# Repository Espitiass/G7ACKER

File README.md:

# 🤖 G7ACKER - Robot Móvil Autónomo con Visión Artificial

Sistema de robot móvil con conducción autónoma basado en visión artificial, diseñado para navegación en entornos estructurados mediante seguimiento de carril, detección de obstáculos y dirección tipo Ackermann.

---

# 📖 Descripción del Proyecto

El proyecto consiste en el desarrollo de un robot móvil autónomo que integra procesamiento visual, sensores de proximidad y control embebido distribuido para lograr un desplazamiento inteligente sin intervención humana.

El sistema está orientado a simular escenarios reales de movilidad autónoma, como vehículos terrestres a pequeña escala que operan sobre carriles definidos.

El enfoque del proyecto combina:

- Visión artificial para percepción del entorno
- Detección de estaciones mediante sensor infrarrojo
- Control distribuido (Raspberry Pi + ESP32)
- Sistema de dirección tipo Ackermann

---

# 🎥 Demo del Sistema

## Funcionamiento del robot

> *(Agregar imágenes, GIF o enlace de video del funcionamiento)*

---

# 🔄 Flujo del Sistema

```text
[Cámara IMX219]
        ↓
[Procesamiento en Raspberry Pi (OpenCV)]
        ↓
[Decisiones de navegación]
        ↓
[ESP32]
        ↓
[Driver TB6612FNG]
        ↓
[Motores JGY-370 + Servo MG90]
```

---

# 🛠️ Hardware del Sistema

## 🧠 Unidad de procesamiento

- Raspberry Pi 5
- ESP32

---

## 📡 Sensores

- Cámara IMX219 (visión artificial)
- Sensor ultrasónico HC-SR04 (detección frontal de obstáculos)
- 1 Sensor infrarrojo TCRT5000 (detección lateral de estaciones de carga y descarga)

---

## ⚙️ Actuadores

- 2 Motores DC JGY-370
- Servo motor MG90 (engranajes metálicos)

---

## 🚗 Sistema de dirección

- Configuración tipo Ackermann

---

## ⚡ Etapa de potencia

- Driver TB6612FNG Dual Motor

---

## 🔋 Alimentación

- Batería LiPo 7.4V – 5A
- Regulador XL4016 (salida a 5V, alta corriente)
- Regulador LM2596 (salida a 3.3V)

---

# 💻 Software y Tecnologías

| Tecnología | Uso |
|---|---|
| Python | Lógica principal y visión artificial |
| OpenCV | Procesamiento de imagen |
| ESP32 (C/C++) | Control embebido |
| Serial USB | Comunicación Raspberry Pi ↔ ESP32 |

---

# 📂 Estructura del Repositorio

```text
G7ACKER/
├── .vscode/                          # Configuración de Visual Studio Code
│   └── settings.json
│
├── docs/                             # Documentación del proyecto
│   ├── acta_constitucion/
│   ├── bitacoras/
│   ├── imagenes/
│   ├── matriz_control_de_documentos/
│   ├── poster/
│   ├── presentacion_final/
│   └── README.md
│
├── hardware/                         # Diseño electrónico y PCB
│   ├── esquematico/
│   ├── pcb/
│   └── README.md
│
├── mechanical/                       # Diseño mecánico y estructural
│   ├── Diseños_de_prueba/
│   ├── Diseños_finales/
│   └── README.md
│
├── src/                              # Código fuente
│   ├── Autonomía_básica/
│   ├── Control_de_motores/
│   ├── Pruebas/
│   └── README.md
│
├── .gitignore
├── LICENSE
├── README.md
├── Scriptsactivate
└── test.jpg
```

---

# 📊 Estado del Proyecto

| Módulo | Estado |
|---|---|
| Diseño electrónico | ✅ Completado |
| PCB | ✅ Fabricada y operativa |
| Sistema mecánico | ✅ Completado |
| Visión artificial | ✅ Integrada y funcional |
| Control autónomo | 🧪 Pruebas finales |

---

# 👥 Autores

| Integrante | Área |
|---|---|
| Sofía Salomé Espitia Jiménez | Área de diseño |
| Vanesa Galeano Franco | Área de programación |
| Julián Andrés García Correa | Área eléctrica y electrónica |
| Jose Lisander Hurtado Castañeda | Área mecánica |

---

# 📄 Licencia

Este proyecto se distribuye bajo la licencia MIT License.

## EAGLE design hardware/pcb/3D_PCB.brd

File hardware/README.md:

# Diseño Electrónico

Esta carpeta contiene el desarrollo del sistema electrónico del robot G7ACKER, incluyendo el diseño del esquemático y la PCB utilizada para la integración del sistema.

---

## Estructura

```text
hardware/
│── esquematico/
│── pcb/
```

---

## Contenido

### Esquemático

Incluye la representación del sistema electrónico antes de su implementación física:

* Imagen del esquemático por medio de ilustración en el sofware DRAW.IO (formato PNG) para visualización rápida
* Archivo original del esquemático (formato `.sch`) con todas las conexiones y componentes definidos
* Imagen del esquematico original en FUSION

Este diseño permite validar la correcta interconexión de los módulos antes de avanzar al diseño de la PCB.

---

### PCB

Contiene el diseño final de la placa electrónica:

* Archivo de la PCB con ruteo completo (formato `.f3z`, Fusion 360)
* Modelo 3D de la PCB (formato `.brd`)
* Imagen del ruto de la pcb en FUSION

Este diseño corresponde a la versión enviada a fabricación, incluyendo:

* Rutas eléctricas
* Distribución de componentes
* Integración del sistema completo

---

## Propósito

* Documentar el diseño electrónico del sistema
* Facilitar la fabricación de la PCB
* Permitir la revisión y modificación del circuito
* Servir como base para futuras iteraciones

---

## Notas

* Mantener consistencia entre esquemático y PCB
* Verificar nombres de componentes y conexiones
* Evitar modificaciones directas sobre versiones finales sin control

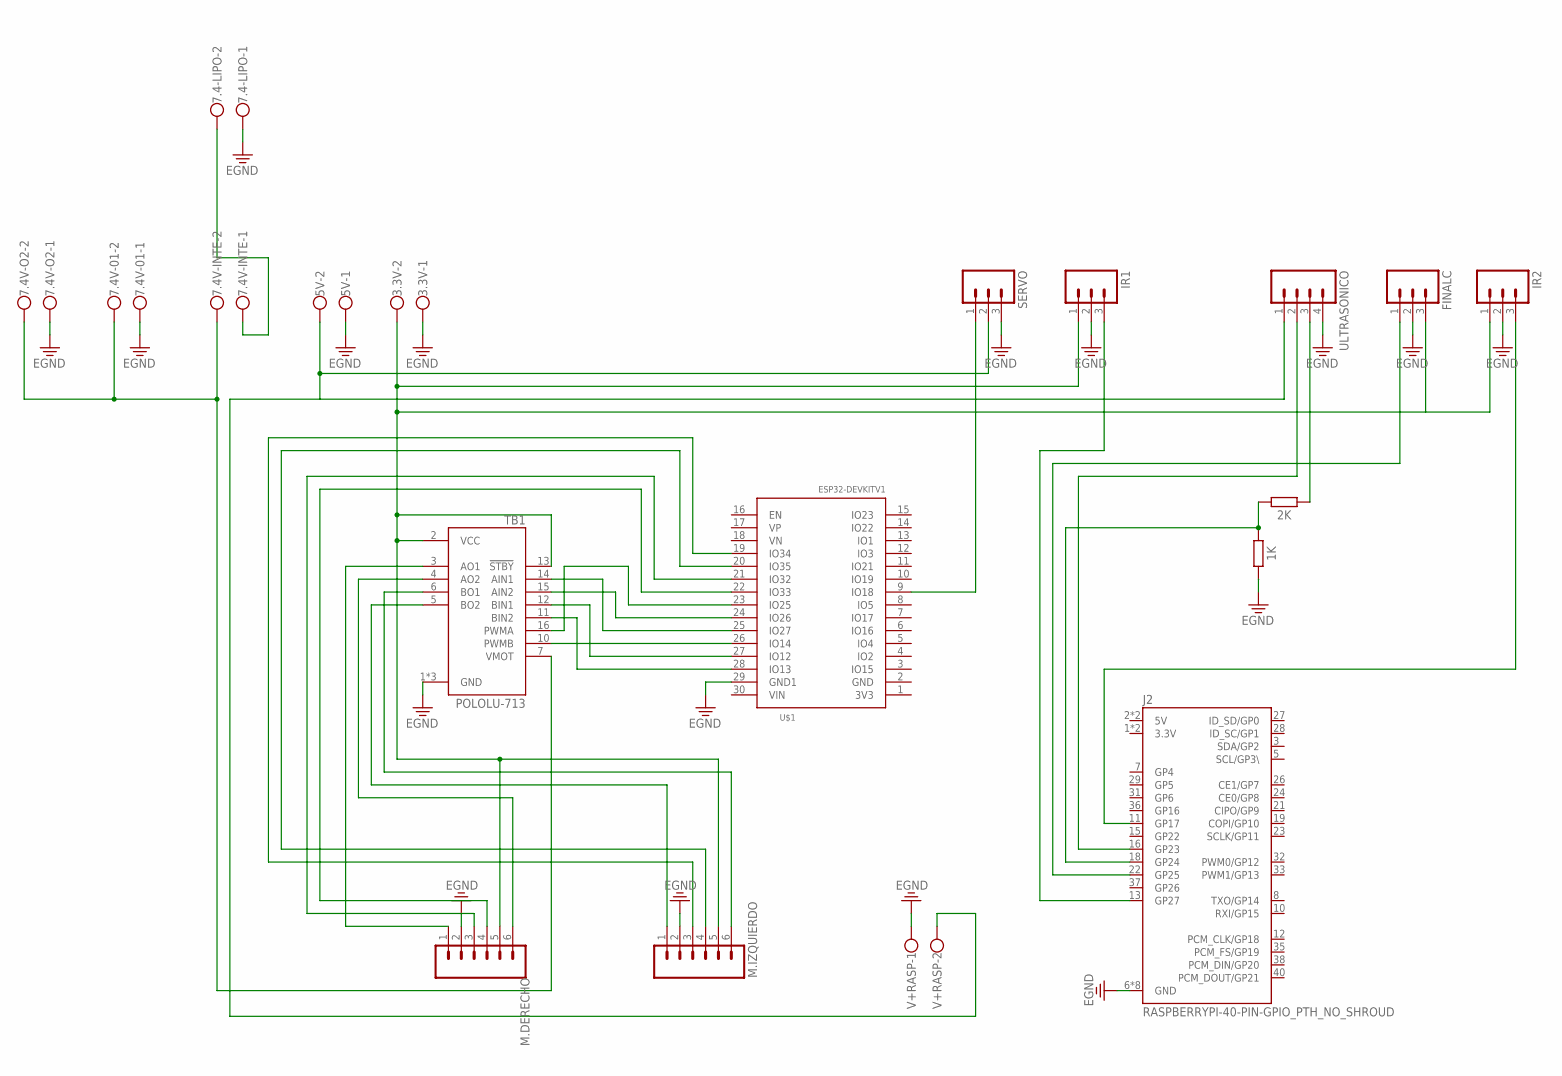
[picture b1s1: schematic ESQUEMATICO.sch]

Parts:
1K, 2K: R_AXIAL-11.7MM-PITCH; RESAD1176W63L850D250B
3.3V, 5V, 7.4-LIPO, 7.4V-01, 7.4V-INTE, 7.4V-O2: W237-102
FINALC: MA03; 03P
IR1, IR2: MA03; 03P
J2: RASPBERRYPI-40-PIN-GPIO_PTH_NO_SHROUD; 2X20
M.DERECHO, M.IZQUIERDO: MA06; 06PA
SERVO: MA03; 03P
TB1: POLOLU-713; SHIELD_POLOLU-713
U$1: ESP32DEVKITV1; ESP32-DEVKITV1
ULTRASONICO: MA04; 04PA
V+RASP: W237-102

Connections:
3.3V: 3.3V.2, FINALC.3, IR1.1, IR2.1, J2.1 (3.3V), J2.17 (3.3V), M.DERECHO.5, M.IZQUIERDO.5, TB1.2 (VCC), TB1.13 (!STBY)
5V: 5V.2, J2.2 (5V), J2.4 (5V), SERVO.2, ULTRASONICO.1, V+RASP.2
7.4V: 7.4-LIPO.2, 7.4V-INTE.1
EGND: 1K.2, 3.3V.1, 5V.1, 7.4-LIPO.1, 7.4V-01.1, 7.4V-O2.1, FINALC.2, IR1.2, IR2.2, J2.6 (GND), J2.9 (GND), J2.14 (GND), J2.20 (GND), J2.25 (GND), J2.30 (GND), J2.34 (GND), J2.39 (GND), M.DERECHO.2, M.IZQUIERDO.2, SERVO.3, TB1.1 (GND), TB1.8 (GND), TB1.9 (GND), U$1.29 (GND1), ULTRASONICO.4, V+RASP.1
M.DERECHO2: 7.4V-01.2, 7.4V-INTE.2, 7.4V-O2.2, TB1.7 (VMOT)
unnamed: TB1.16 (PWMA), U$1.23 (IO25)
unnamed: TB1.10 (PWMB), U$1.26 (IO14)
unnamed: TB1.11 (BIN2), U$1.28 (IO13)
unnamed: TB1.12 (BIN1), U$1.27 (IO12)
unnamed: TB1.15 (AIN2), U$1.24 (IO26)
unnamed: TB1.14 (AIN1), U$1.25 (IO27)
unnamed: M.DERECHO.1, TB1.3 (AO1)
unnamed: M.DERECHO.6, TB1.4 (AO2)
unnamed: M.IZQUIERDO.6, TB1.6 (BO1)
unnamed: M.IZQUIERDO.1, TB1.5 (BO2)
unnamed: M.DERECHO.3, U$1.21 (IO32)
unnamed: M.DERECHO.4, U$1.22 (IO33)
unnamed: M.IZQUIERDO.3, U$1.19 (IO34)
unnamed: M.IZQUIERDO.4, U$1.20 (IO35)
unnamed: SERVO.1, U$1.9 (IO18)
unnamed: IR2.3, J2.11 (GP17)
unnamed: IR1.3, J2.13 (GP27)
unnamed: J2.16 (GP23), ULTRASONICO.2
unnamed: FINALC.1, J2.22 (GP25)
unnamed: 1K.1, 2K.2, J2.18 (GP24)
unnamed: 2K.1, ULTRASONICO.3

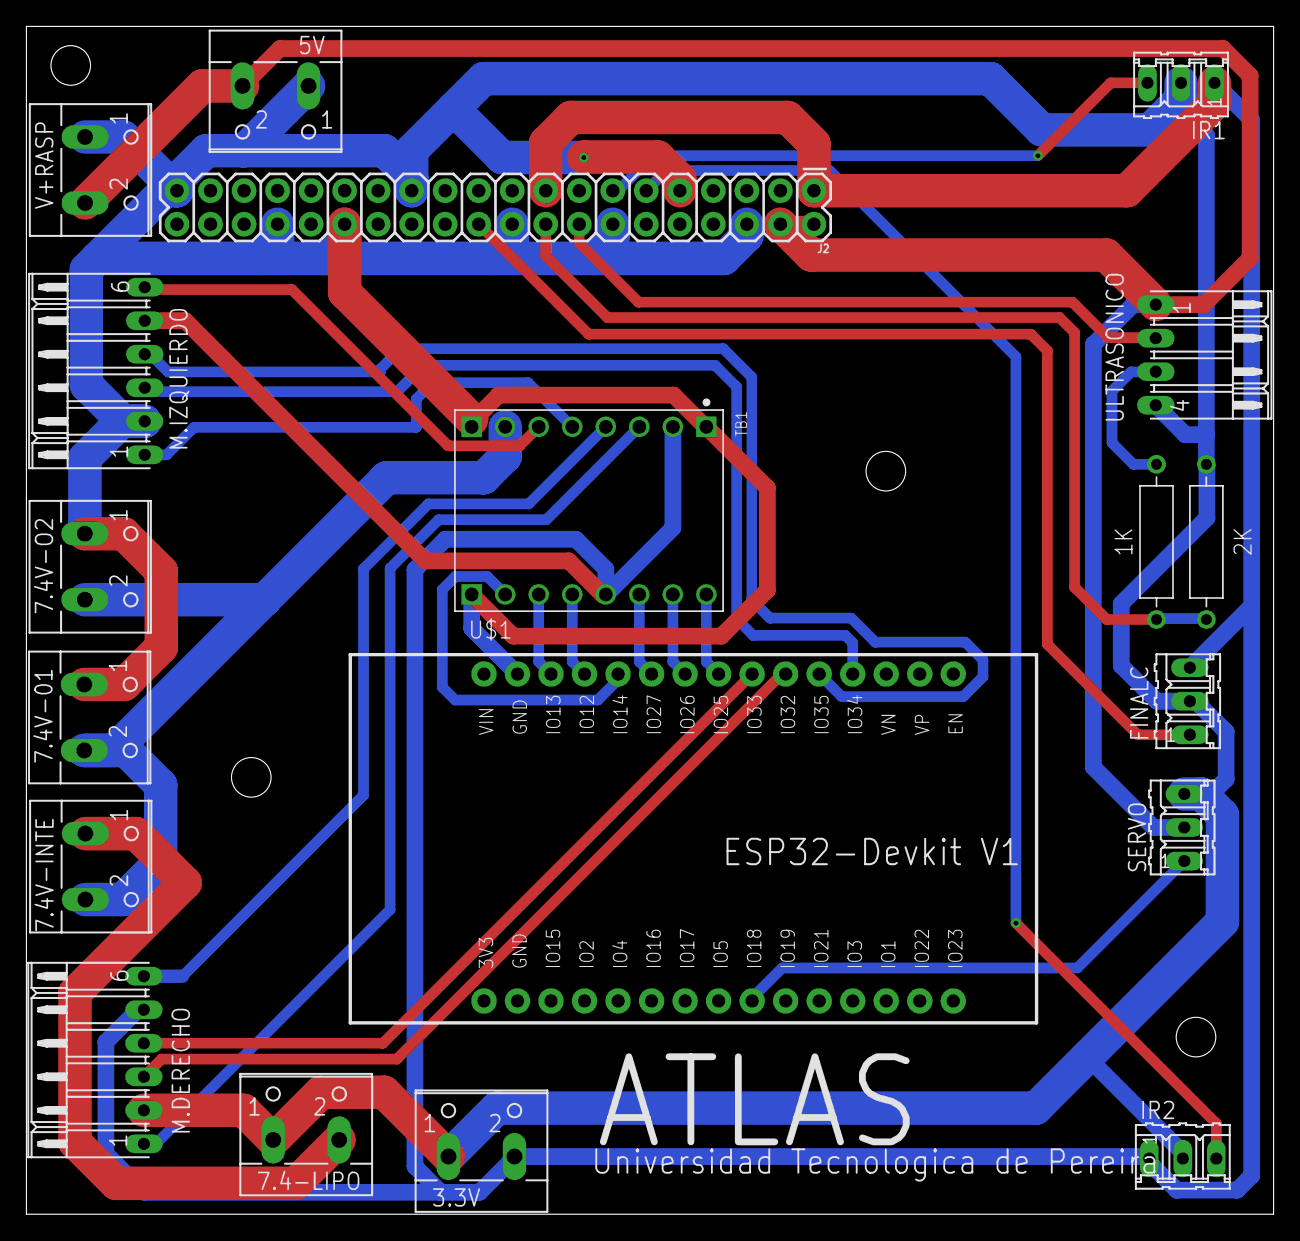
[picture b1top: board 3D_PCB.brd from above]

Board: 2 copper layers, 94.5 x 90.0 mm, 19 parts (0 on the bottom side), 26 nets.

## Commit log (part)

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2026-02-20 creacion de archivos readme
2026-02-21 codigo de prueba
2026-03-11 control de motores y encoder
2026-03-11 prueba_motor_encoder
2026-03-12 DISEÑOS
2026-03-12 motores
2026-03-12 Agrega servidor y actualiza prueba1
2026-03-12 Cambios en las carpetas para organizar mejor
2026-03-12 cambio de nombres raiz
2026-03-12 cambios en el nombre de la carpeta documentacion
2026-03-12 creacion readme
2026-03-12 Add README.md for Diseño Mecánico/Direccion
2026-03-12 Add project link to README.md
2026-03-12 cambios de archivos stl a readme
2026-03-12 nuevo mensaje
2026-03-12 traccion
2026-03-13 documentacion de mecanica
2026-03-13 imagenes insertadas
2026-03-13 imagenes
2026-03-13 documentacion traccion
2026-03-13 documentacion de los codigos
2026-03-13 actualizacion en la documentación
2026-03-13 organizacion repositorio principal
2026-03-13 cambios en documentacion
2026-03-13 cambios en el apartado principal
2026-03-13 actualizacion
2026-03-20 eliminacion de codigos que no se usan
2026-03-20 codigos nuevos
2026-03-20 comunicacion raspberry con esp32
2026-03-20 eliminacion de un codigo
2026-03-21 Create Fotos-Videos
2026-04-04 Create FI-F-001 BITÁCORA SEMANA 8 Y 9
2026-04-07 detencion_linea_obstaculos
2026-04-09 camara_2
2026-04-10 nuevos codigos
2026-04-10 nuevos
2026-04-13 Rename FI-F-001 BITÁCORA SEMANA 6 Y 7.docx.pdf to FI-F-001_BITACORA_SEMANA_6_Y_7_PLANEACION.docx.pdf
2026-04-13 Rename FI-F-001 BITÁCORA SEMANA 8 Y 9 (1).pdf to FI-F-001_BITACORA_SEMANA_8_Y_9_EJECUCION.pdf
2026-04-13 Rename FI-F-001 BITÁCORA SEMANA 6 Y 7.docx (1).pdf to FI-F-001_BITACORA_SEMANA_6_Y_7_EJECUCION.docx
2026-04-13 Rename FI-F-001_BITACORA_SEMANA_6_Y_7_EJECUCION.docx to FI-F-001 BITÁCORA SEMANA 6 Y 7 EJECUCIÓN.docx
2026-04-14 nuevo_codigos2
2026-04-14 Create codigo_camara_actualizado
2026-04-14 Create contro_esp32_actualizado
2026-04-14 Rename Dirección.md to direccion_v1.md
2026-04-14 Rename Tracción.md to traccion_v1.md
2026-04-14 pull
2026-04-14 nueva version del codigo de obstaculo camara
2026-04-15 nueva version de codigo v2
2026-04-16 nuevos cambios en codigos
2026-04-17 cambios codigos v3
2026-04-17 cambios codigo v4
2026-04-17 nuevas carpetas y orden nuevo en la carpeta src acerca de los codigos de la raspberry
2026-04-17 cambios en el codigo 1.2
2026-04-17 cambios en el README
2026-04-18 cambios en el codigo obstaculos 2.1
2026-04-20 cambios en el umbral
2026-04-20 cambios en el codigo 2.1
2026-04-24 cambios en codigo 2.1
2026-04-24 cambios en 2.1
2026-04-24 nuevos cambios en codigos de ultrasonidos
2026-04-24 CAMBIOS
2026-04-28 cambios guardados
2026-04-28 cambios en codigo 2.2
2026-04-28 cambios en el codigo 2.2
2026-04-28 aumento de roi
2026-04-28 nuevos codifgos para lectura de qr
2026-04-28 codigo de qr
2026-04-29 cambios en 2.2
2026-05-09 WIP: guardar cambios locales antes de reparar .git
2026-05-11 codigo nuevo para probar lectura de qr nuevos
2026-05-12 nueva logica con nuevos qr
2026-05-12 cambios en control motor
2026-05-19 Cambios en la carpeta src programacion
2026-05-19 cambios en el src
2026-05-19 nuevos cambios en la carpeta de pruebas
2026-05-19 cambio en la carpeta pruebas
2026-05-19 actualizaciones en readme
2026-05-19 nuevos readme en cada carpeta de codigo
2026-05-19 readme control de motores
2026-05-19 nuevos readme en la carpeta mechanical
2026-05-20 cambios en v2 de programacion
2026-05-20 cambios en motor
2026-05-21 cambios src
2026-05-21 cambios en qr logic
2026-05-21 cambios en codigos src
2026-05-22 ir para funcionar
2026-05-22 fuera tag 9
2026-05-22 lee hasta tag 9
2026-05-22 hasta la inter del tag 9
2026-05-22 hasta la inter del tag 9 y regresa al incio, primera estacion de descarga lista
2026-05-22 afinacion de lectura de tag
2026-05-22 afinacion de primera interseccion
2026-05-22 lista descarga 2 y descarga 3
2026-05-26 presentacion
2026-05-26 eliminacion de V3
2026-05-26 nueva version
2026-05-26 main
2026-05-26 nuevo contraldor PI
2026-05-27 cambio control
2026-05-27 interseccion 2 afinamiento
2026-05-27 cambios en inter 2
2026-05-27 inter 2 mejorar la eliminacion de la dos lineas
2026-05-28 codigo con inter buena, lipo 8 v ajustar seg
2026-05-28 nuevo codigo de la esp32 y de V3 para hacer interseccion con endoders
2026-05-28 intersecciones con encoders
2026-05-28 cambios en el tag 10 para continuar el proceso
2026-05-29 deteccion qr mejorada circuito completo
2026-05-29 codigo listo con encoders en intersecciones
2026-05-29 codigo listo con encoders en las inter
2026-05-29 CI2 con cinco seg de 90 grados
2026-06-05 cambios en la carpeta src
2026-06-05 cambios en documentos
2026-06-05 actualizacion src v3
2026-06-05 documentos finales

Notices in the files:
parts and their libraries:
SparkFun-Connectors: Licensing: Creative Commons ShareAlike 4.0 International - https://creativecommons.org/licenses/by-sa/4.0
